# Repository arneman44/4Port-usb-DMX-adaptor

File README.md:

4Port usb DMX adaptor

As a beginning lighting tech at my local youth club. I needed a cheap way to control some lighting fixtures via DMX. That's why I created this USB-DMX dongle that's open-source so my fellow DIYers can build one themself. I will be selling these as PCB's, kits, and assembled units. At what I find a very reasonable price.

More info can be found on: https://nortle.be/15-diy-4-port-usb-dmx/

i used JCLPCB for ordering pcb's:
https://jlcpcb.com/

<p xmlns:dct="http://purl.org/dc/terms/" xmlns:cc="http://creativecommons.org/ns#" class="license-text"><span rel="dct:title">4 Port USB to DMX adaptor</span> by <a rel="cc:attributionURL dct:creator" property="cc:attributionName" href="www.nortle.be">Arne Van den Broeck</a> is licensed under <a rel="license" href="https://creativecommons.org/licenses/by-nc-sa/4.0">CC BY-NC-SA 4.0</a></p>

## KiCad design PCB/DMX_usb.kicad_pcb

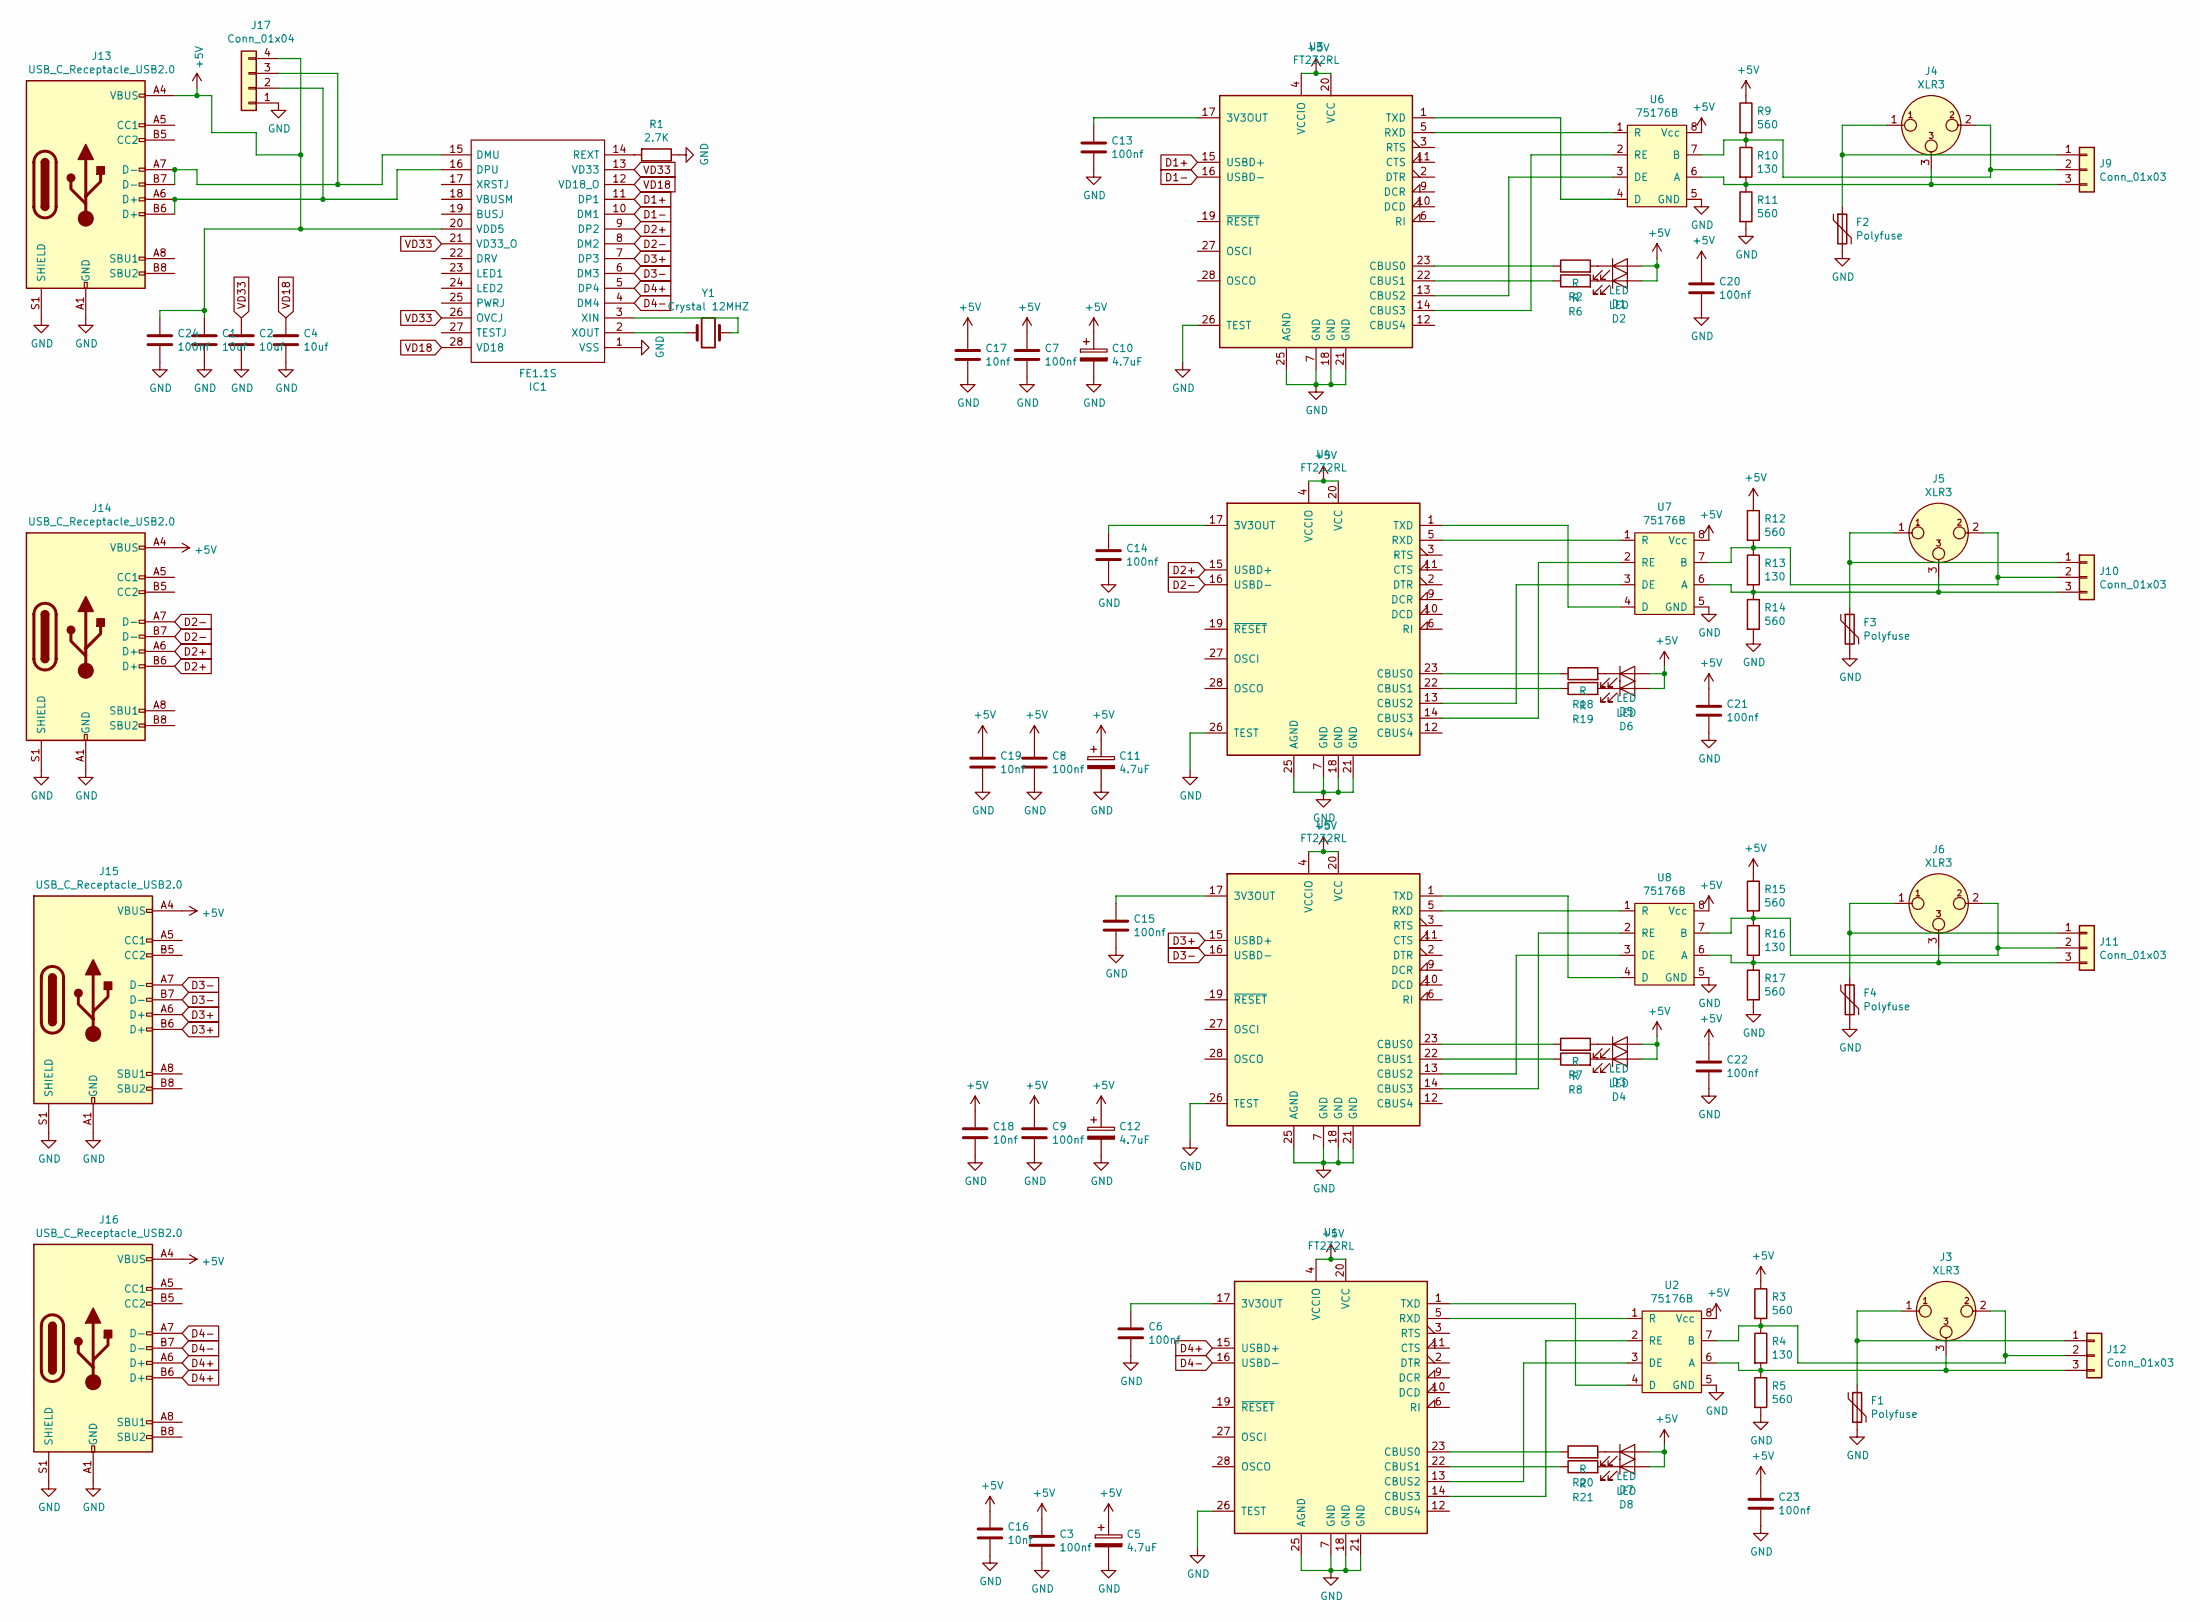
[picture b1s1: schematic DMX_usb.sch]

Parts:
C1, C2, C4: 10uf; C_0805_2012Metric_Pad1.15x1.40mm_HandSolder
C3, C6, C7, C8, C9, C13, C14, C15, C20, C21, C22, C23, C24: 100nf; C_0805_2012Metric_Pad1.15x1.40mm_HandSolder
C5, C10, C11, C12: 4.7uF; CP_Elec_4x5.4
C16, C17, C18, C19: 10nf; C_0805_2012Metric_Pad1.15x1.40mm_HandSolder
D1, D2, D3, D4, D5, D6, D7, D8: LED; LED_0805_2012Metric_Pad1.15x1.40mm_HandSolder
F1, F2, F3, F4: Polyfuse; Fuse_1206_3216Metric_Pad1.42x1.75mm_HandSolder
IC1: FE1.1S; SOP64P600X175-28N; Manufacturer_Part_Number FE1.1S
J3, J4, J5, J6: XLR3; Jack_XLR_Neutrik_NC3FAH1_Horizontal
J9, J10, J11, J12: Conn_01x03; PinSocket_1x03_P2.54mm_Vertical
J13, J14, J15, J16: USB_C_Receptacle_USB2.0; USB_C_Receptacle_Palconn_UTC16-G
J17: Conn_01x04; PinSocket_1x04_P2.54mm_Vertical
R1: 2.7K; C_0805_2012Metric_Pad1.15x1.40mm_HandSolder
R2, R6, R7, R8, R18, R19, R20, R21: R; R_0805_2012Metric_Pad1.15x1.40mm_HandSolder
R3, R5, R9, R11, R12, R14, R15, R17: 560; C_0805_2012Metric_Pad1.15x1.40mm_HandSolder
R4, R10, R13, R16: 130; C_0805_2012Metric_Pad1.15x1.40mm_HandSolder
U1, U3, U4, U5: FT232RL; SSOP-28_5.3x10.2mm_P0.65mm
U2, U6, U7, U8: 75176B; SOIC-8_3.9x4.9mm_P1.27mm
Y1: Crystal 12MHZ; Crystal_SMD_HC49-SD

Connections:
+5V: C1.1, C3.1, C5.1, C7.1, C8.1, C9.1, C10.1, C11.1, C12.1, C16.1, C17.1, C18.1, C19.1, C20.1, C21.1, C22.1, C23.1, C24.1, D1.2 (A), D2.2 (A), D3.2 (A), D4.2 (A), D5.2 (A), D6.2 (A), D7.2 (A), D8.2 (A), IC1.20 (VDD5), J13.A4 (VBUS), J13.A9 (VBUS), J13.B4 (VBUS), J13.B9 (VBUS), J14.A4 (VBUS), J14.A9 (VBUS), J14.B4 (VBUS), J14.B9 (VBUS), J15.A4 (VBUS), J15.A9 (VBUS), J15.B4 (VBUS), J15.B9 (VBUS), J16.A4 (VBUS), J16.A9 (VBUS), J16.B4 (VBUS), J16.B9 (VBUS), J17.4, R3.1, R9.1, R12.1, R15.1, U1.4 (VCCIO), U1.20 (VCC), U2.8 (Vcc), U3.4 (VCCIO), U3.20 (VCC), U4.4 (VCCIO), U4.20 (VCC), U5.4 (VCCIO), U5.20 (VCC), U6.8 (Vcc), U7.8 (Vcc), U8.8 (Vcc)
D1+: IC1.11 (DP1), U3.15 (USBD+)
D1-: IC1.10 (DM1), U3.16 (USBD-)
D2+: IC1.9 (DP2), J14.A6 (D+), J14.B6 (D+), U4.15 (USBD+)
D2-: IC1.8 (DM2), J14.A7 (D-), J14.B7 (D-), U4.16 (USBD-)
D3+: IC1.7 (DP3), J15.A6 (D+), J15.B6 (D+), U5.15 (USBD+)
D3-: IC1.6 (DM3), J15.A7 (D-), J15.B7 (D-), U5.16 (USBD-)
D4+: IC1.5 (DP4), J16.A6 (D+), J16.B6 (D+), U1.15 (USBD+)
D4-: IC1.4 (DM4), J16.A7 (D-), J16.B7 (D-), U1.16 (USBD-)
GND: C1.2, C2.2, C3.2, C4.2, C5.2, C6.2, C7.2, C8.2, C9.2, C10.2, C11.2, C12.2, C13.2, C14.2, C15.2, C16.2, C17.2, C18.2, C19.2, C20.2, C21.2, C22.2, C23.2, C24.2, F1.2, F2.2, F3.2, F4.2, IC1.1 (VSS), J13.A1 (GND), J13.A12 (GND), J13.B1 (GND), J13.B12 (GND), J13.S1 (SHIELD), J14.A1 (GND), J14.A12 (GND), J14.B1 (GND), J14.B12 (GND), J14.S1 (SHIELD), J15.A1 (GND), J15.A12 (GND), J15.B1 (GND), J15.B12 (GND), J15.S1 (SHIELD), J16.A1 (GND), J16.A12 (GND), J16.B1 (GND), J16.B12 (GND), J16.S1 (SHIELD), J17.1, R1.1, R5.2, R11.2, R14.2, R17.2, U1.7 (GND), U1.18 (GND), U1.21 (GND), U1.25 (AGND), U1.26 (TEST), U2.5 (GND), U3.7 (GND), U3.18 (GND), U3.21 (GND), U3.25 (AGND), U3.26 (TEST), U4.7 (GND), U4.18 (GND), U4.21 (GND), U4.25 (AGND), U4.26 (TEST), U5.7 (GND), U5.18 (GND), U5.21 (GND), U5.25 (AGND), U5.26 (TEST), U6.5 (GND), U7.5 (GND), U8.5 (GND)
unnamed: C6.1, U1.17 (3V3OUT)
unnamed: C13.1, U3.17 (3V3OUT)
unnamed: C14.1, U4.17 (3V3OUT)
unnamed: C15.1, U5.17 (3V3OUT)
unnamed: D1.1 (K), R2.2
unnamed: D2.1 (K), R6.2
unnamed: D3.1 (K), R7.2
unnamed: D4.1 (K), R8.2
unnamed: D5.1 (K), R18.2
unnamed: D6.1 (K), R19.2
unnamed: D7.1 (K), R20.2
unnamed: D8.1 (K), R21.2
unnamed: F1.1, J3.1, J12.1
unnamed: F2.1, J4.1, J9.1
unnamed: F3.1, J5.1, J10.1
unnamed: F4.1, J6.1, J11.1
unnamed: IC1.2 (XOUT), Y1.1
unnamed: IC1.3 (XIN), Y1.2
unnamed: IC1.14 (REXT), R1.2
unnamed: IC1.15 (DMU), J13.A7 (D-), J13.B7 (D-), J17.3
unnamed: IC1.16 (DPU), J13.A6 (D+), J13.B6 (D+), J17.2
unnamed: J4.2, J9.2, R9.2, R10.1, U6.7 (B)
unnamed: J4.3, J9.3, R10.2, R11.1, U6.6 (A)
unnamed: J5.2, J10.2, R12.2, R13.1, U7.7 (B)
unnamed: J5.3, J10.3, R13.2, R14.1, U7.6 (A)
unnamed: J6.2, J11.2, R15.2, R16.1, U8.7 (B)
unnamed: J6.3, J11.3, R16.2, R17.1, U8.6 (A)
unnamed: J3.2, J12.2, R3.2, R4.1, U2.7 (B)
unnamed: J3.3, J12.3, R4.2, R5.1, U2.6 (A)
unnamed: R2.1, U3.23 (CBUS0)
unnamed: R6.1, U3.22 (CBUS1)
unnamed: R7.1, U5.23 (CBUS0)
unnamed: R8.1, U5.22 (CBUS1)
unnamed: R18.1, U4.23 (CBUS0)
unnamed: R19.1, U4.22 (CBUS1)
unnamed: R20.1, U1.23 (CBUS0)
unnamed: R21.1, U1.22 (CBUS1)
unnamed: U1.1 (TXD), U2.4 (D)
unnamed: U1.5 (RXD), U2.1 (R)
unnamed: U1.13 (CBUS2), U2.3 (DE)
unnamed: U1.14 (CBUS3), U2.2 (RE)
unnamed: U3.1 (TXD), U6.4 (D)
unnamed: U3.5 (RXD), U6.1 (R)
unnamed: U3.13 (CBUS2), U6.3 (DE)
unnamed: U3.14 (CBUS3), U6.2 (RE)
unnamed: U4.1 (TXD), U7.4 (D)
unnamed: U4.5 (RXD), U7.1 (R)
unnamed: U4.13 (CBUS2), U7.3 (DE)
unnamed: U4.14 (CBUS3), U7.2 (RE)
unnamed: U5.1 (TXD), U8.4 (D)
unnamed: U5.5 (RXD), U8.1 (R)
unnamed: U5.13 (CBUS2), U8.3 (DE)
unnamed: U5.14 (CBUS3), U8.2 (RE)
VD18: C4.1, IC1.12 (VD18_O), IC1.28 (VD18)
VD33: C2.1, IC1.13 (VD33), IC1.21 (VD33_O), IC1.26 (OVCJ)

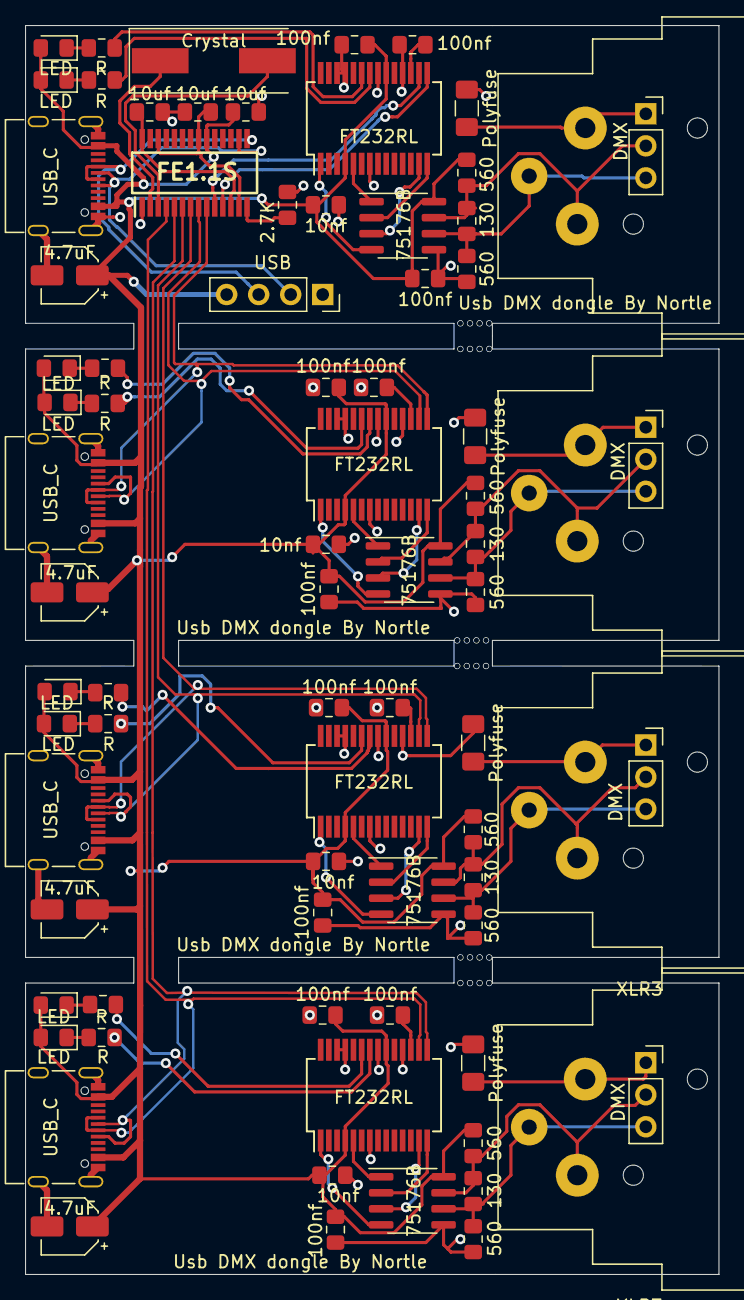
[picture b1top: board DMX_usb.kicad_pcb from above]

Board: 2 copper layers, 55.0 x 99.1 mm, 79 parts (0 on the bottom side), 65 nets.

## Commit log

2020-06-25 add PCB files
    V1 PCB
2020-06-25 restructure PCB files
2020-07-11 V1 version
2020-08-12 v2
    fixed some stupid problems with pcb desgn
